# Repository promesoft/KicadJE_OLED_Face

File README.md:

# KicadJE_OLED_Face
Faceplate for uP that uses I2C SSD1306
# Purpose
Faceplate for uProcessor controlled eurorack units with an SSD1306 OLED display, two rotary dials/pots, two audio inputs, two cv inputs and two outputs.
## Board 1
Adjustment:

Gate Input

CV Input

Input Audio 

Output Audio  

# Status - Received
## Initial 
| Stage  | Detail | Status |
| ------------- | ------------- | ------------- |
| create material  | sch |OK
| | pcb |OK
| | gerber |OK
| production |  |  
|  | produced  |OK 
|  | delivered |OK
## Preliminary validation
| Test  | Detail | Status |
| ------------- | ------------- | ------------- |
| Initial Inspection | | ok |
| Mechanical Inspection | | ok - does not match I/O and controls with earlier boards|
| Initial Technical Test | Board 1 |  |
| Initial Product Test | Board1 |  |

## Secondary validation
| Test  | Detail | Status |
| ------------- | ------------- |------------- |
| Product Test | 1 | |
| Quality | 1 | |
| Long Term Product Test |  |  |
| Power Draw |  | 

## Errata
### Errata - 

## Issues and Notes
### 

# Pictures

# Schematic
## Sch 1

# Analysis
## Diag 1

## Prototype

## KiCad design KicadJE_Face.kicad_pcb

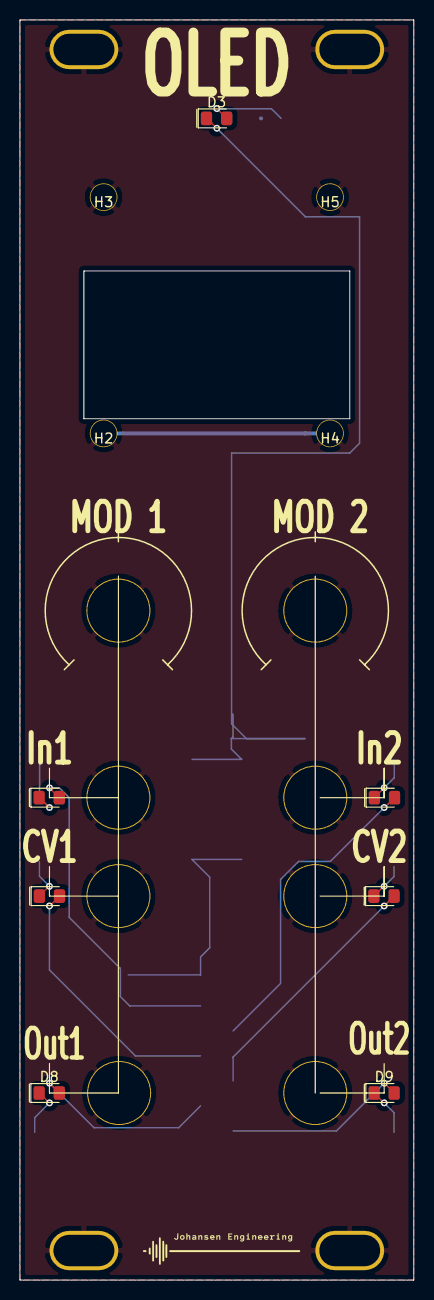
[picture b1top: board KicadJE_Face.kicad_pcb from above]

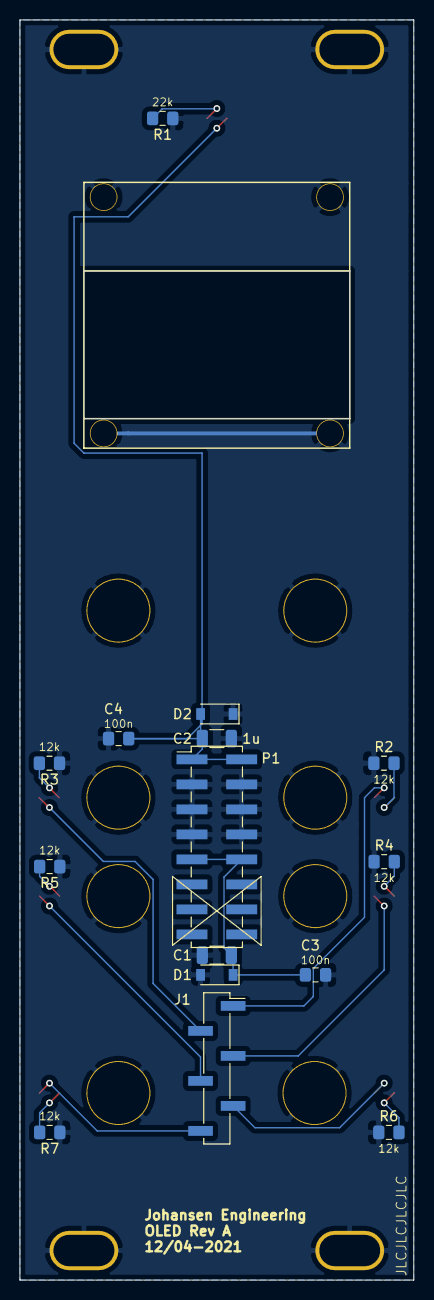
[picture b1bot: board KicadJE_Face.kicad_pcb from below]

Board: 2 copper layers, 40.0 x 128.0 mm, 39 parts (17 on the bottom side), 19 nets.

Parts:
C1, C2: 1u; C_1206_3216Metric
C3, C4: 100n; C_0805_AJ
D1, D2: 1N1007; D_SOD-123
D3, D4, D5, D6, D7, D8, D9: LED; D_0805_AJ
H1: ON; LED_Hole_3mm
H2, H3, H4, H5: OLED; M2.7_Plated
H6, H7, H8, H9: MountingHole_Pad; MountingHole_Eurorack3
J1: LED 1-6; PinHeader_1x06_P2.54mm_Vertical_SMD_Pin1Right
P1: Doepfer_Power_16pin; PinHeader_2x08_P2.54mm_Vertical_SMD
R1: 22k; R_0805_AJ
R2, R3, R4, R5, R6, R7: 12k; R_0805_AJ
TP102: SQ; Jack_6m3
TP103: In1; Jack_6m3
TP105: In3; Jack_6m3
TP106: HS; Jack_6m3
TP107: OFF1; Pot_6m3_scale1
TP107#2: FM; Jack_6m3
TP108: PWM; Jack_6m3
TP112: Fine; Pot_6m3_scale1

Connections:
+5V: P1.11, P1.12
+12VA: C1.1, C3.1, D1.1, P1.9, P1.10
-12VA: C2.2, C4.2, D2.2, D3.1, P1.1, P1.2
GND: C1.2, C2.1, C3.2, C4.1, D1.2, D2.1, H2.1, H3.1, H4.1, H5.1, H6.1, H7.1, H8.1, H9.1, P1.3, P1.4, P1.5, P1.6, P1.7, P1.8, R1.1, R2.1, R3.1, R4.1, R5.1, R6.1, R7.1, TP102.1, TP103.1, TP105.1, TP106.1, TP107.1, TP107#2.1, TP108.1, TP112.1
unnamed: D3.2, R1.2
unnamed: D4.1, R2.2
unnamed: D4.2, J1.1
unnamed: D5.1, R3.2
unnamed: D5.2, J1.2
unnamed: D6.1, R4.2
unnamed: D6.2, J1.3
unnamed: D7.1, R5.2
unnamed: D7.2, J1.4
unnamed: D8.1, R6.2
unnamed: D8.2, J1.5
unnamed: D9.1, R7.2
unnamed: D9.2, J1.6
unnamed: P1.13, P1.14
unnamed: P1.15, P1.16

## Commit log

2021-04-12 Created from TEMPLATE
2021-04-12 Schematic init
2021-04-12 6LED
2021-04-12 Mouting holes to pads - DRC
2021-04-12 Gerber
2021-04-12 Faceplate
